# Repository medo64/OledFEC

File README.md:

# OLED Framework Expansion Card

Framework computer expansion card that allows a USB CDC serial connection to
SSD1306 OLED display modules.

## Pinout

To connect to this board, one has to use a 4-pin JST XH connector. The following
table represents the pinout, pin 1 being on the left as looking into the
expansion card.

| # | Ref   | Description                     |
|--:|:-----:|---------------------------------|
| 1 | GND   | Ground connection               |
| 2 | 5V    | OLED power                      |
| 2 | SCL   | I²C clock                       |
| 3 | SDA   | I²C data                        |

As power consumption is low, wires can be almost any AWG. I would recommend
using 24 AWG wire 0.25 mm² as they allow for greater compatibility with other
connectors.

## LEDs

LED will blink on UART communication with computer (both sending toward and
receiving data from computer).

## Protocol

This driver will present itself to the system as CDC USB device. Communication
protocol is text-based and available [here](https://github.com/medo64/UsbOled.Firmware).

---

*You can check my blog and other projects at [www.medo64.com](https://www.medo64.com/electronics/).*

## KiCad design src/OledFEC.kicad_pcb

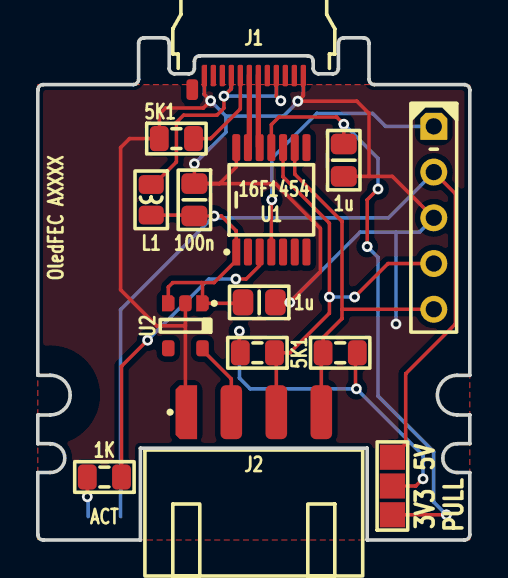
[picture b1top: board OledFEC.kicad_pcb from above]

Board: 2 copper layers, 24.0 x 27.9 mm, 15 parts (1 on the bottom side), 14 nets.

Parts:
C1: 100n; C (0805)
C2, C3: 1u; C (0805)
DS1: ACT; DS (0805)
ICSP: Microchip PIC; ICSP PIC Pogo (5w)
J1: 105444-0001; J USB C 3.2 Edge (24w)
J2: B4B-XH-A; J JST XH Edge [OLED] (4w)
JP1: Jumper; JP Dual (1205)
L1: 40R; L (0805)
R1: 1K; R (0805)
R2, R3, R4: 5K1; R (0805)
U1: 16F1454; U Micro [PIC16F1454] (TSSOP-14)
U2: MIC2005A-1; U LoadSwitch 100mA [MIC2091-1] (SOT23-5)

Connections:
3V3: C2.2, JP1.1, U1.11
5V: C1.2, C3.2, DS1.2, ICSP.2, JP1.3, L1.2, U1.1, U2.1, U2.3
5V_USB: J1.A4, J1.A9, J1.B04, J1.B09, L1.1
A_CC: J1.A5, R2.2
GND: C1.1, C2.1, C3.1, ICSP.3, J1.A1, J1.A12, J1.B01, J1.B12, J2.1, R2.1, U1.14, U2.2
ICSP_VPP: ICSP.1, U1.4
LED_ACTIVE: DS1.1, R1.2
OLED_5V: J2.2, U2.5
OLED_SCL: ICSP.4, J2.3, R3.1, U1.10
OLED_SDA: ICSP.5, J2.4, R4.1, U1.9
OUT_LED_ACTIVE: R1.1, U1.3
PULL_UP: JP1.2, R3.2, R4.2
USB_DM: J1.A7, U1.12
USB_DP: J1.A6, U1.13

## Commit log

2024-08-22 Using MIC2091-1 instead of MIC2005A-1
2024-08-28 Cleanup
2024-08-28 Added pull-up jumper
2024-08-28 Added pinout
2024-08-28 Updated pull-up resistors to be populated
